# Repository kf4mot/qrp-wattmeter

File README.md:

# HF QRP directional wattmeter
A compact directional wattmeter for portable operation. Forward and reflected power is shown simultaneously with 2 LED bargraphs for easy antenna tuning.
Power sensing is done with a tandem match wound on a BN43-202 core. The microcontroller is a ATmega32u4 with USB interface for firmware uploading and serial data out (PC logging, debugging, etc).

[Created with KiCAD ver. 5.0.2](https://kicad.org)

**Things worth knowing**

1. **Firmware is incomplete**. I've been able to do basic hardware checks, but actual power measurement and calibration isn't done.
1. Diodes D1-2, D4-5, and D6-7 are for providing forward bias to the bridge to improve linearity and remove zero offset. 2 devices are shown in each position to give the builder the option of a PTH or SMD package.
1. Op-amps U1 and U2 have PTH and SMD package footprints.
1. The board was designed to fit the Polycase JB-35 enclosure. **Untested** https://www.polycase.com/jb-35 https://github.com/kf4mot/qrp-wattmeter/blob/master/docs/14531129045666870.pdf 

[Licensed under CERN-OHL-S V2. Julian White, 2020](https://www.ohwr.org/project/cernohl/wikis/home)

[Schematic](https://github.com/kf4mot/qrp-wattmeter/blob/master/hardware/qrp_wattmeter.pdf)

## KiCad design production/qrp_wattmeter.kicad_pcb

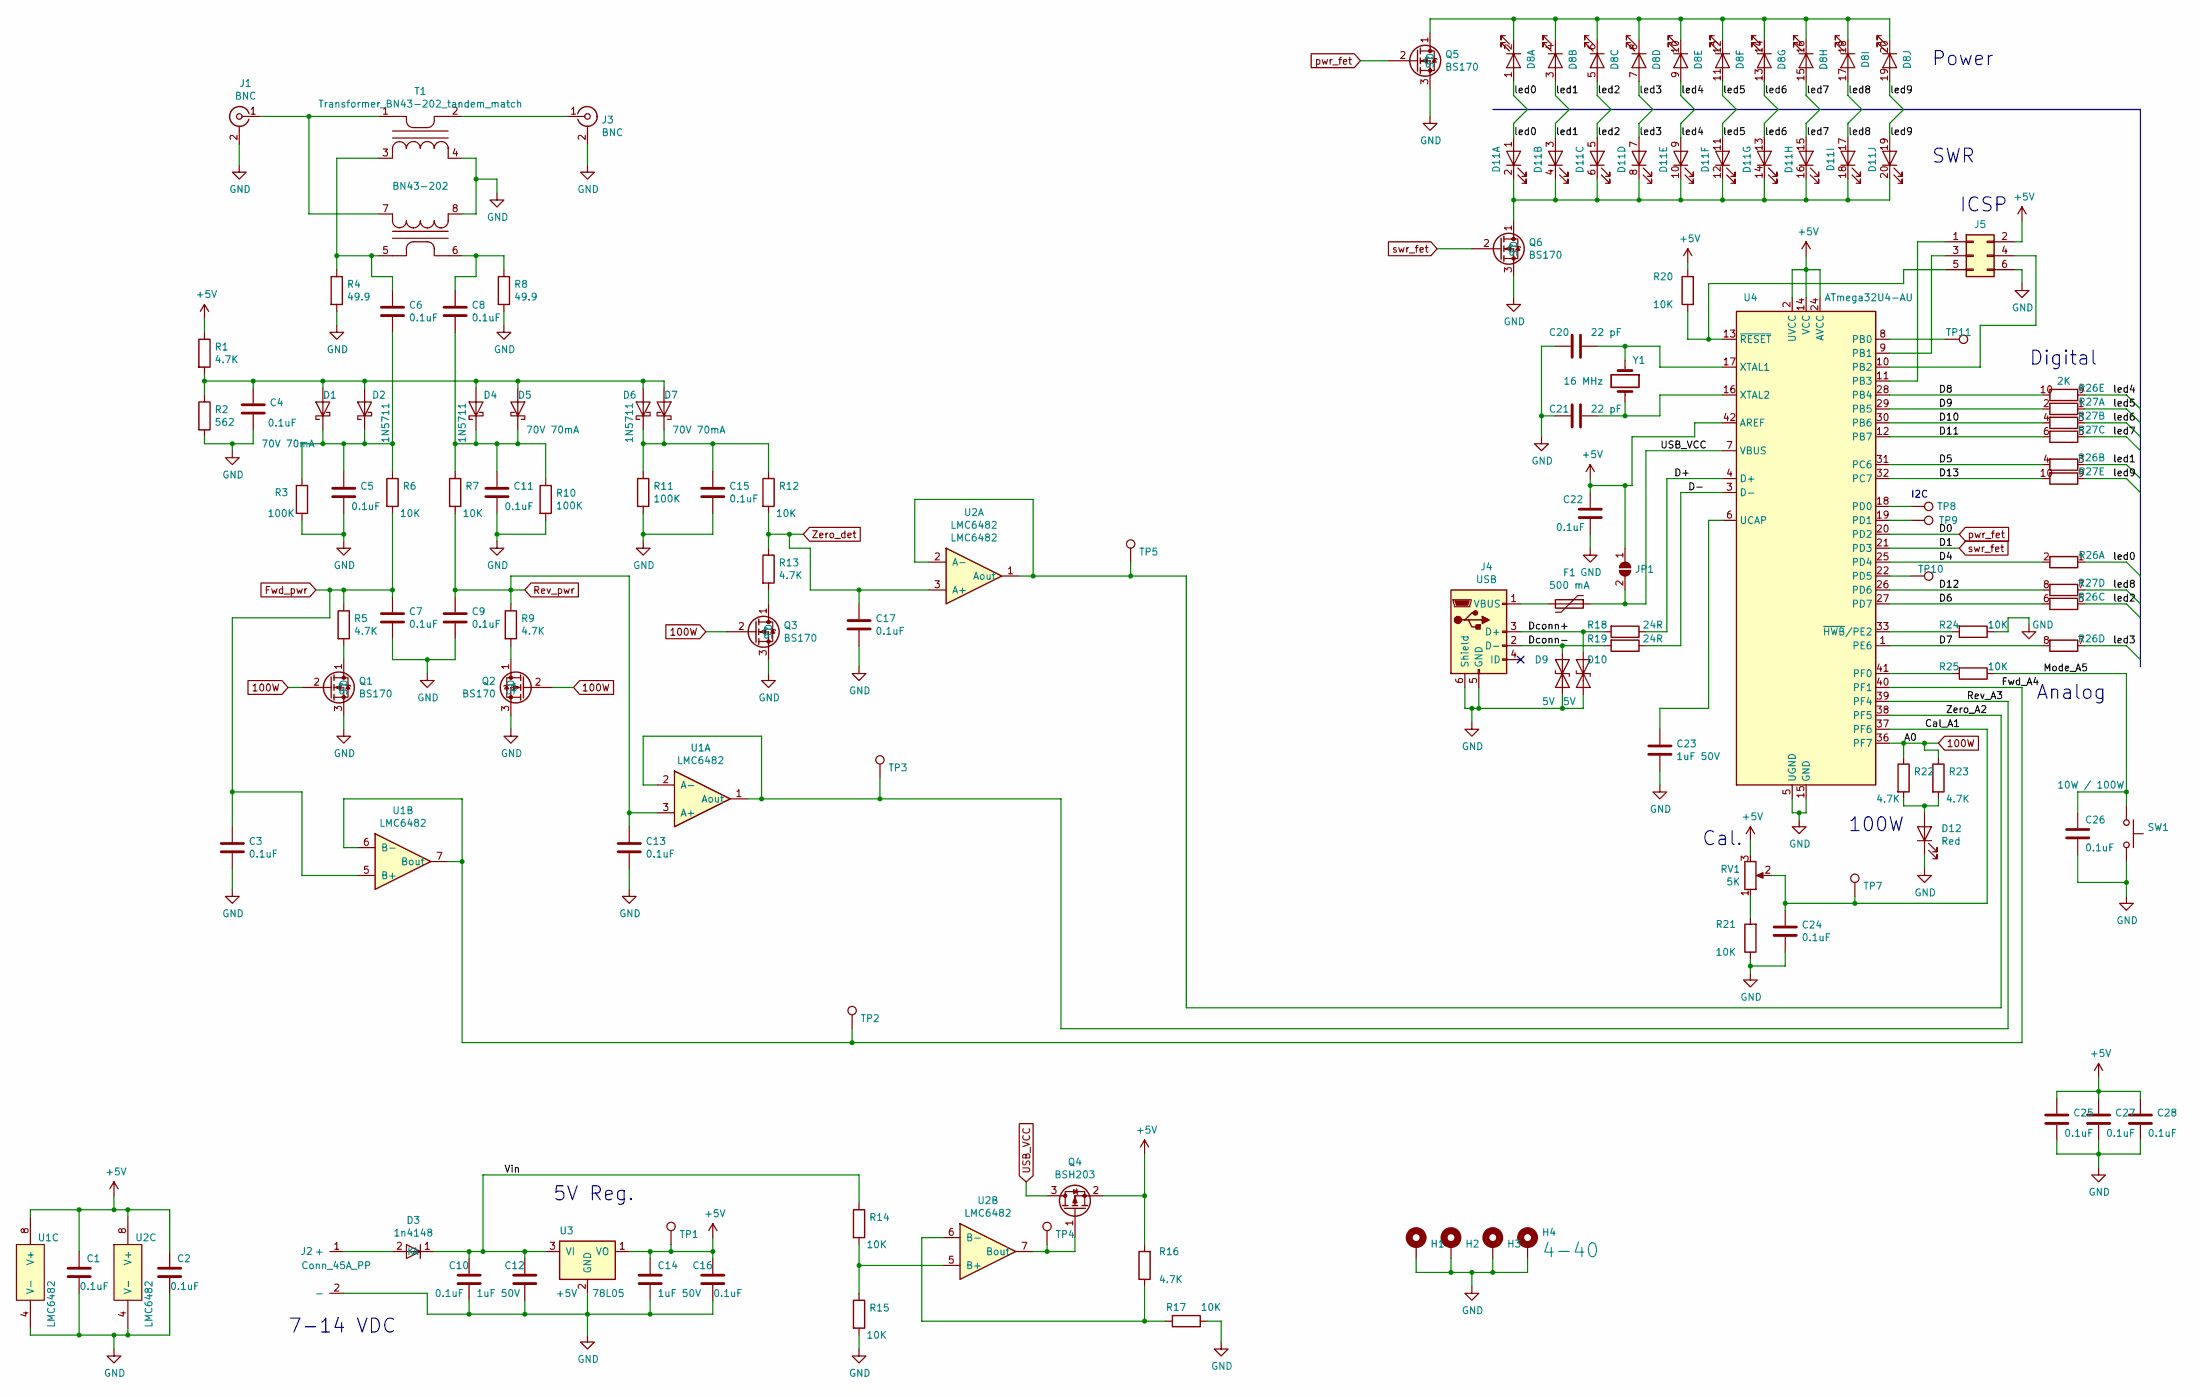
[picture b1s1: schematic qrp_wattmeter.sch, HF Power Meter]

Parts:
C1, C2, C3, C4, C5, C6, C7, C8, C9, C10, C11, C13, C15, C16, C17, C22, C24, C25, C26, C27, C28: C_0.1uF_50V_5mm; C_Disc_D4.7mm_W2.5mm_P5.00mm; Part Number K104K15X7RF53H5
C12, C14, C23: C_1uF_50V_0805_x7r; C_0805_HandSoldering; Part Number UMK212BJ105KG-T
C20, C21: C_22pF_0603_50V; C_0603_HandSoldering; Part Number GRM1885C1H220JA01D
D1, D5, D7: D_Schottky_BAS70H; D_SOD-123F; Part Number BAS70H,115
D2, D4, D6: 1N5711; D_DO-35_SOD27_P7.62mm_Horizontal
D3: 1n4148; D_DO-41_SOD81_P10.16mm_Horizontal; Part Number 1n4148
D8, D11: LED_Lumex_SSA_10X_Red; Lumex_SSA-LXH1025ID_10X_led; Part Number SSA-LXH1025ID
D9, D10: D_TVS_5V_ESD9B5.0ST5G; D_SOD-923; Part Number ESD9B5.0ST5G
D12: LED_3mm_Red; LED_D3.0mm; Part Number LTL-4221N
F1: Polyfuse_500mA; Fuse_SMD1812; Part Number MF-MSMF050-2
H1, H2, H3, H4: MountingHole_Pad_4-40; MountingHole_4-40_Pad
J1, J3: BNC; bnc_molex_0731375003; Part Number 0731375003
J2: Conn_45A_PP; PP45_RA_pcb; Part Number 2X 1336G1 and 1X 114555P2
J4: USB_B_Micro; USB_Micro-B_Molex-105017-0001; Part Number 105017-0001
J5: ICSP_header; Pin_Header_Straight_2x03_Pitch2.54mm
JP1: SolderJumper_2_Open; GS2
Q1, Q2, Q3, Q5, Q6: BS170; TO-92_Molded_Wide; Part Number BS170-D27Z
Q4: BSH203; SOT-23_Handsoldering; Part Number BSH203,215
R1, R5, R9, R13, R16, R22, R23: R_4.7K_6.3mm; R_Axial_DIN0207_L6.3mm_D2.5mm_P10.16mm_Horizontal; Part Number MFR-25FTF52-4K7
R2: R_562_6.3mm; R_Axial_DIN0207_L6.3mm_D2.5mm_P10.16mm_Horizontal; Part Number MFR-25FBF52-562R
R3, R10, R11: R_100K_6.3mm; R_Axial_DIN0207_L6.3mm_D2.5mm_P10.16mm_Horizontal; Part Number MFR-25FTF52-100K
R4, R8: R_49.9_2W_th; R_Axial_DIN0414_L11.9mm_D4.5mm_P20.32mm_Horizontal; Part Number MOS2CT52R49R9F
R6, R7, R12, R14, R15, R17, R20, R21, R24, R25: R_10K_6.3mm; R_Axial_DIN0207_L6.3mm_D2.5mm_P10.16mm_Horizontal; Part Number MFR-25FRF52-10K
R18, R19: R_24_sm1206; R_1206_HandSoldering; Part Number CR1206-FX-24R0ELF
R26, R27: R_Array_5X_2K_TH; R_Array_SIP10; Part Number 4610X-102-202LF
RV1: R_POT_5K_3306F-1-502; Pot_Bourns_3306F; Part Number 3306F-1-502
SW1: SW_Push_TH; PINHEAD1-2; Part Number Generic Push Button
T1: Transformer_BN43-202_tandem_match; Transformer_Amidon-BN43-202; Part Number BN43-202
TP1, TP2, TP3, TP4, TP5, TP7, TP8, TP9, TP10, TP11: Test_smt; tpsm
U1, U2: LMC6482; DIP-8+SOIC-8; Part Number LMC6482IMX/NOPB
U3: 78L05; TO-92_Inline_Wide; Part Number L78L05ABZ-TR
U4: ATmega32U4-AU; LQFP-44_10x10mm_Pitch0.8mm; Part Number ATMEGA32U4-AU
Y1: Crystal_16M_SMT; Crystal_SMD_HC49-SD; Part Number ECS-160-20-3X-TR

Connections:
100W: Q1.2 (G), Q2.2 (G), Q3.2 (G), R22.1, R23.1, U4.36 (PF7)
+5V: C1.1, C2.1, C14.1, C16.1, C22.1, C25.1, C27.1, C28.1, J5.2, JP1.1 (A), Q4.2 (S), R1.1, R16.2, R20.2, RV1.3, TP1.1, U1.8 (V+), U2.8 (V+), U3.1 (VO), U4.2 (UVCC), U4.14 (VCC), U4.24 (AVCC), U4.34 (VCC), U4.42 (AREF), U4.44 (AVCC)
/Cal_A1: C24.1, RV1.2, TP7.1, U4.37 (PF6)
/D4: R26.2, U4.25 (PD4)
/D5: R26.4, U4.31 (PC6)
/D6: R26.6, U4.27 (PD7)
/D7: R26.8, U4.1 (PE6)
/D8: R26.10, U4.28 (PB4)
/D9: R27.2, U4.29 (PB5)
/D10: R27.4, U4.30 (PB6)
/D11: R27.6, U4.12 (PB7)
/D12: R27.8, U4.26 (PD6)
/D13: R27.10, U4.32 (PC7)
/D+: R18.1, U4.4 (D+)
/D-: R19.1, U4.3 (D-)
/Dconn+: D10.1 (A1), J4.3 (D+), R18.2
/Dconn-: D9.1 (A1), J4.2 (D-), R19.2
/Fwd_A4: TP2.1, U1.6 (B-), U1.7 (Bout), U4.40 (PF1)
/Mode_A5: C26.1, R25.1, SW1.1
/Rev_A3: TP3.1, U1.1 (Aout), U1.2 (A-), U4.39 (PF4)
/Vin: C10.1, C12.1, D3.1 (K), R14.1, U3.3 (VI)
/Zero_A2: TP5.1, U2.1 (Aout), U2.2 (A-), U4.38 (PF5)
/led0: D8.1 (A), D11.1 (A), R26.1
/led1: D8.3 (A), D11.3 (A), R26.3
/led2: D8.5 (A), D11.5 (A), R26.5
/led3: D8.7 (A), D11.7 (A), R26.7
/led4: D8.9 (A), D11.9 (A), R26.9
/led5: D8.11 (A), D11.11 (A), R27.1
/led6: D8.13 (A), D11.13 (A), R27.3
/led7: D8.15 (A), D11.15 (A), R27.5
/led8: D8.17 (A), D11.17 (A), R27.7
/led9: D8.19 (A), D11.19 (A), R27.9
Fwd_pwr: C3.1, C7.1, R5.1, R6.2, U1.5 (B+)
GND: C1.2, C2.2, C3.2, C4.2, C5.2, C7.2, C9.2, C10.2, C11.2, C12.2, C13.2, C14.2, C15.2, C16.2, C17.2, C20.2, C21.2, C22.2, C23.2, C24.2, C25.2, C26.2, C27.2, C28.2, D9.2 (A2), D10.2 (A2), D12.1 (K), H1.1, H2.1, H3.1, H4.1, J1.2 (Ext), J2.2 (-), J3.2 (Ext), J4.5 (GND), J4.6 (Shield), J5.6, Q1.3 (S), Q2.3 (S), Q3.3 (S), Q5.3 (S), Q6.3 (S), R2.2, R3.2, R4.2, R8.2, R10.2, R11.2, R15.2, R17.1, R21.1, R24.1, SW1.2, T1.4 (SB), T1.8 (SB), U1.4 (V-), U2.4 (V-), U3.2 (GND), U4.5 (UGND), U4.15 (GND), U4.23 (GND), U4.35 (GND), U4.43 (GND)
unnamed: C4.1, D1.2 (A), D2.2 (A), D4.2 (A), D5.2 (A), D6.2 (A), D7.2 (A), R1.2, R2.1
unnamed: C5.1, C6.2, D1.1 (K), D2.1 (K), R3.1, R6.1
unnamed: C6.1, R4.1, T1.3 (SA), T1.5 (AB)
unnamed: C8.1, R8.1, T1.6 (AA)
unnamed: C8.2, C11.1, D4.1 (K), D5.1 (K), R7.1, R10.1
unnamed: C15.1, D6.1 (K), D7.1 (K), R11.1, R12.1
unnamed: C20.1, U4.17 (XTAL1), Y1.1
unnamed: C21.1, U4.16 (XTAL2), Y1.2
unnamed: C23.1, U4.6 (UCAP)
unnamed: D3.2 (A), J2.1 (+)
unnamed: D8.2 (K), D8.4 (K), D8.6 (K), D8.8 (K), D8.10 (K), D8.12 (K), D8.14 (K), D8.16 (K), D8.18 (K), D8.20 (K), Q5.1 (D)
unnamed: D11.2 (K), D11.4 (K), D11.6 (K), D11.8 (K), D11.10 (K), D11.12 (K), D11.14 (K), D11.16 (K), D11.18 (K), D11.20 (K), Q6.1 (D)
unnamed: D12.2 (A), R22.2, R23.2
unnamed: F1.2, J4.1 (VBUS)
unnamed: J1.1 (In), T1.1 (AB), T1.7 (SA)
unnamed: J3.1 (In), T1.2 (AA)
unnamed: J5.1, U4.11 (PB3)
unnamed: J5.3, U4.9 (PB1)
unnamed: J5.4, U4.10 (PB2)
unnamed: J5.5, R20.1, U4.13 (~RESET)
unnamed: Q1.1 (D), R5.2
unnamed: Q2.1 (D), R9.2
unnamed: Q3.1 (D), R13.2
unnamed: Q4.1 (G), TP4.1, U2.7 (Bout)
unnamed: R14.2, R15.1, U2.5 (B+)
unnamed: R16.1, R17.2, U2.6 (B-)
unnamed: R21.2, RV1.1
unnamed: R24.2, U4.33 (~HWB~/PE2)
unnamed: R25.2, U4.41 (PF0)
unnamed: TP8.1, U4.18 (PD0)
unnamed: TP9.1, U4.19 (PD1)
unnamed: TP10.1, U4.22 (PD5)
unnamed: TP11.1, U4.8 (PB0)
Rev_pwr: C9.1, C13.1, R7.2, R9.1, U1.3 (A+)
USB_VCC: F1.1, JP1.2 (B), Q4.3 (D), U4.7 (VBUS)
Zero_det: C17.1, R12.2, R13.1, U2.3 (A+)
pwr_fet: Q5.2 (G), U4.20 (PD2)
swr_fet: Q6.2 (G), U4.21 (PD3)

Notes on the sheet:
ICSP
Power
SWR
Analog
100W
Cal.
I2C
Digital
5V Reg.
7-14 VDC

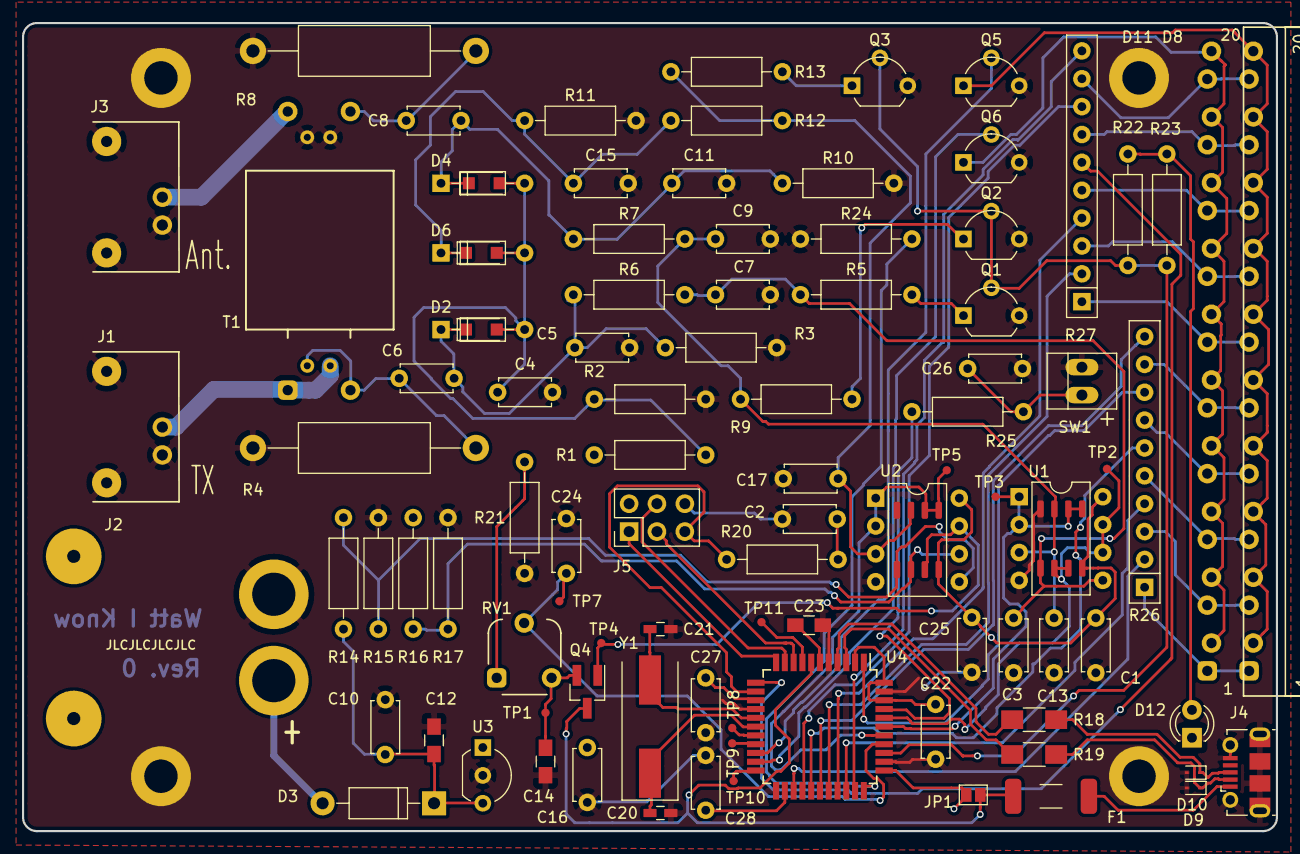
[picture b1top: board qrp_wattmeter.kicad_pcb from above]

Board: 2 copper layers, 114.3 x 73.7 mm, 100 parts (0 on the bottom side), 72 nets.

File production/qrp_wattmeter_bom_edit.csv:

Component,Part,References,Quantity Per PCB,Part Number,MFG,dsp_value
1,C_0.1uF_50V_5mm,C1 C2 C3 C4 C5 C6 C7 C8 C9 C10 C11 C13 C15 C16 C17 C22 C24 C25 C26 C27 C28,21,K104K15X7RF53H5,Vishay,0.1uF
2,C_1uF_50V_0805_x7r,C12 C14 C23,3,UMK212BJ105KG-T,Taiyo Yuden,1uF 50V
3,C_22pF_0603_50V,C20 C21,2,GRM1885C1H220JA01D,Murata,22 pF
4,1N5711,D2 D4 D6,3,,,
5,1n4148,D3,1,1n4148,,
6,D_Schottky_BAS70H,D1 D5 D7,3,"BAS70H,115",NXP,70V 70mA
7,D_TVS_5V_ESD9B5.0ST5G,D9 D10,2,ESD9B5.0ST5G,On Semi,5V
8,LED_3mm_Red,D12,1,LTL-4221N,Lite ON,Red
9,LED_Lumex_SSA_10X_Red,D8 D11,2,SSA-LXH1025ID,Lumex,
10,Polyfuse_500mA,F1,1,MF-MSMF050-2,Bourns,500 mA
11,BNC,J1 J3,2,731375003,Molex,
12,Conn_45A_PP,J2,1,2X 1336G1 and 1X 114555P2,Anderson,
13,ICSP_header,J5,1,,,
14,USB_B_Micro,J4,1,105017-0001,Molex,USB
15,SolderJumper_2_Open,JP1,1,,,
16,BS170,Q1 Q2 Q3 Q5 Q6,5,BS170-D27Z,On Semi,
17,BSH203,Q4,1,"BSH203,215",NXP,
18,R_100K_6.3mm,R3 R10 R11,3,MFR-25FTF52-100K,Yageo,100K
19,R_10K_6.3mm,R6 R7 R12 R14 R15 R17 R20 R21 R24 R25,10,MFR-25FRF52-10K,Yageo,10K
20,R_24_sm1206,R18 R19,2,CR1206-FX-24R0ELF,Bourns,24R
21,R_4.7K_6.3mm,R1 R5 R9 R13 R16 R22 R23,7,MFR-25FTF52-4K7,Yageo,4.7K
22,R_49.9_2W_th,R4 R8,2,MOS2CT52R49R9F,KOA,49.9
23,R_562_6.3mm,R2,1,MFR-25FBF52-562R,Yageo,562
24,R_Array_5X_2K_TH,R26 R27,2,4610X-102-202LF,Bourns,2K
25,R_POT_5K_3306F-1-502,RV1,1,3306F-1-502,Bourns,5K
26,SW_Push_TH,SW1,1,Generic Push Button,,10W / 100W
27,Transformer_BN43-202_tandem_match,T1,1,BN43-202,,
28,78L05,U3,1,L78L05ABZ-TR,ST Micro,+5V
29,ATmega32U4-AU,U4,1,ATMEGA32U4-AU,Atmel,ATMEGA32U4
30,LMC6482,U1 U2,2,LMC6482IMX/NOPB,TI,LMC6482
31,Crystal_16M_SMT,Y1,1,ECS-160-20-3X-TR,ECS,16 MHz

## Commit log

2021-11-08 Update README.md
    https://forum.kicad.info/t/warning-avoid-all-links-to-kicad-pcb-org-use-kicad-org/31521
